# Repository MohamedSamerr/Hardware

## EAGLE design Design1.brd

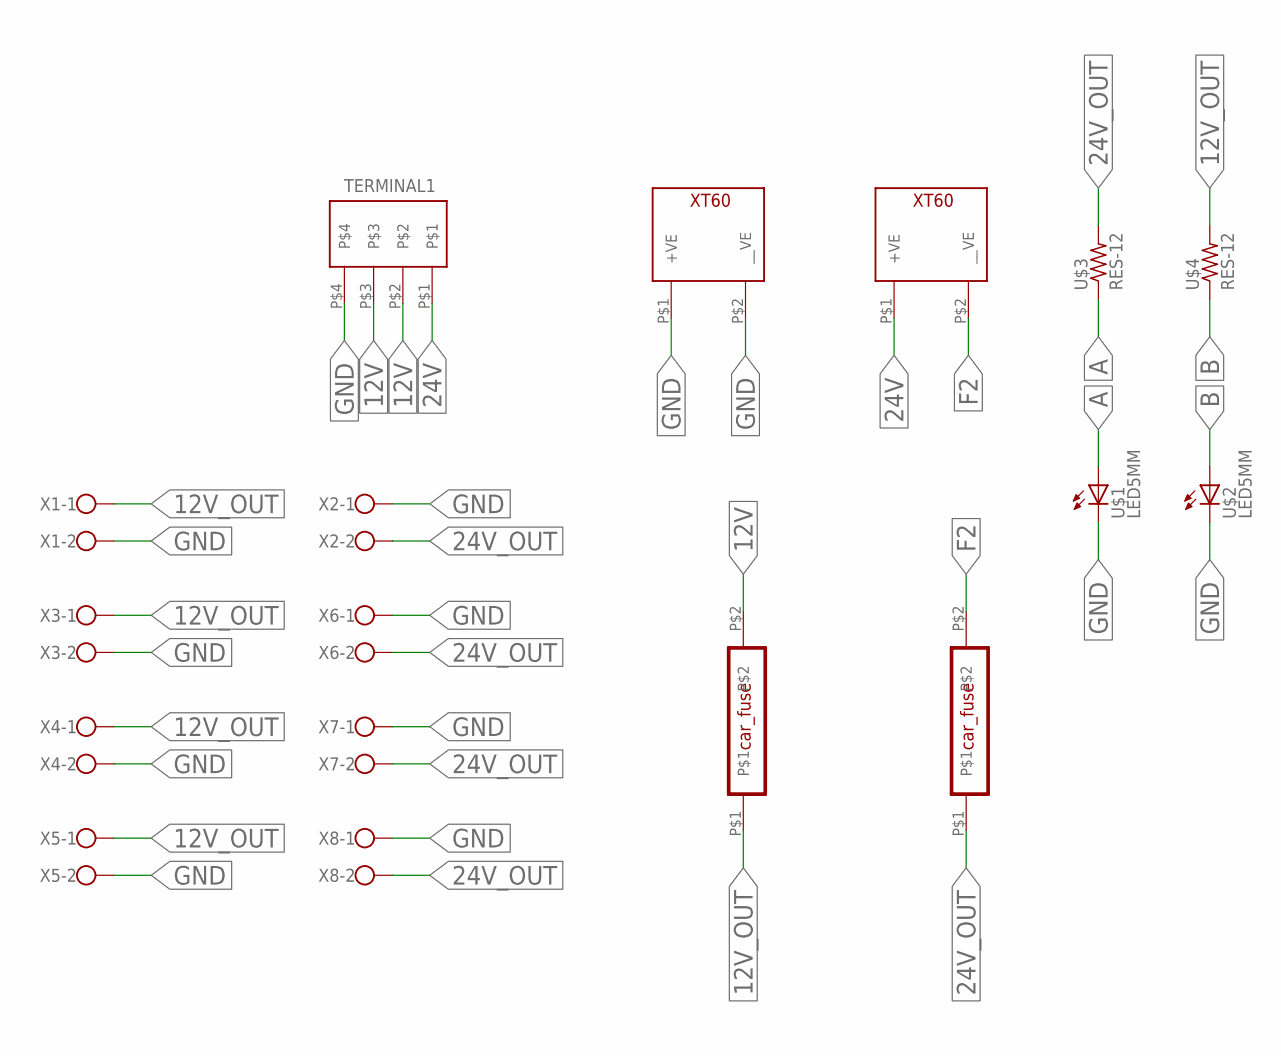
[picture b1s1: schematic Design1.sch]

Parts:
FUSE_12, FUSE_24: CAR_FUSE
SWITCH_12, SWITCH_24: XT60_CONNECTOR; XT60
TERMINAL1: BARRIER_TERMINAL_BLOCK_4PIN_9.5MM
U$1, U$2: LED5MM
U$3, U$4: RES-12; 0207/12
X1, X2, X3, X4, X5, X6, X7, X8: ROSTA.POWER; W239-302

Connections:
12V: FUSE_12.P$2, TERMINAL1.P$2, TERMINAL1.P$3
12V_OUT: FUSE_12.P$1, U$4.2, X1.1, X3.1, X4.1, X5.1
24V: SWITCH_24.P$1 (+VE), TERMINAL1.P$1
24V_OUT: FUSE_24.P$1, U$3.2, X2.2, X6.2, X7.2, X8.2
A: U$1.A, U$3.1
B: U$2.A, U$4.1
F2: FUSE_24.P$2, SWITCH_24.P$2 (__VE)
GND: SWITCH_12.P$1 (+VE), SWITCH_12.P$2 (__VE), TERMINAL1.P$4, U$1.K (C), U$2.K (C), X1.2, X2.1, X3.2, X4.2, X5.2, X6.1, X7.1, X8.1

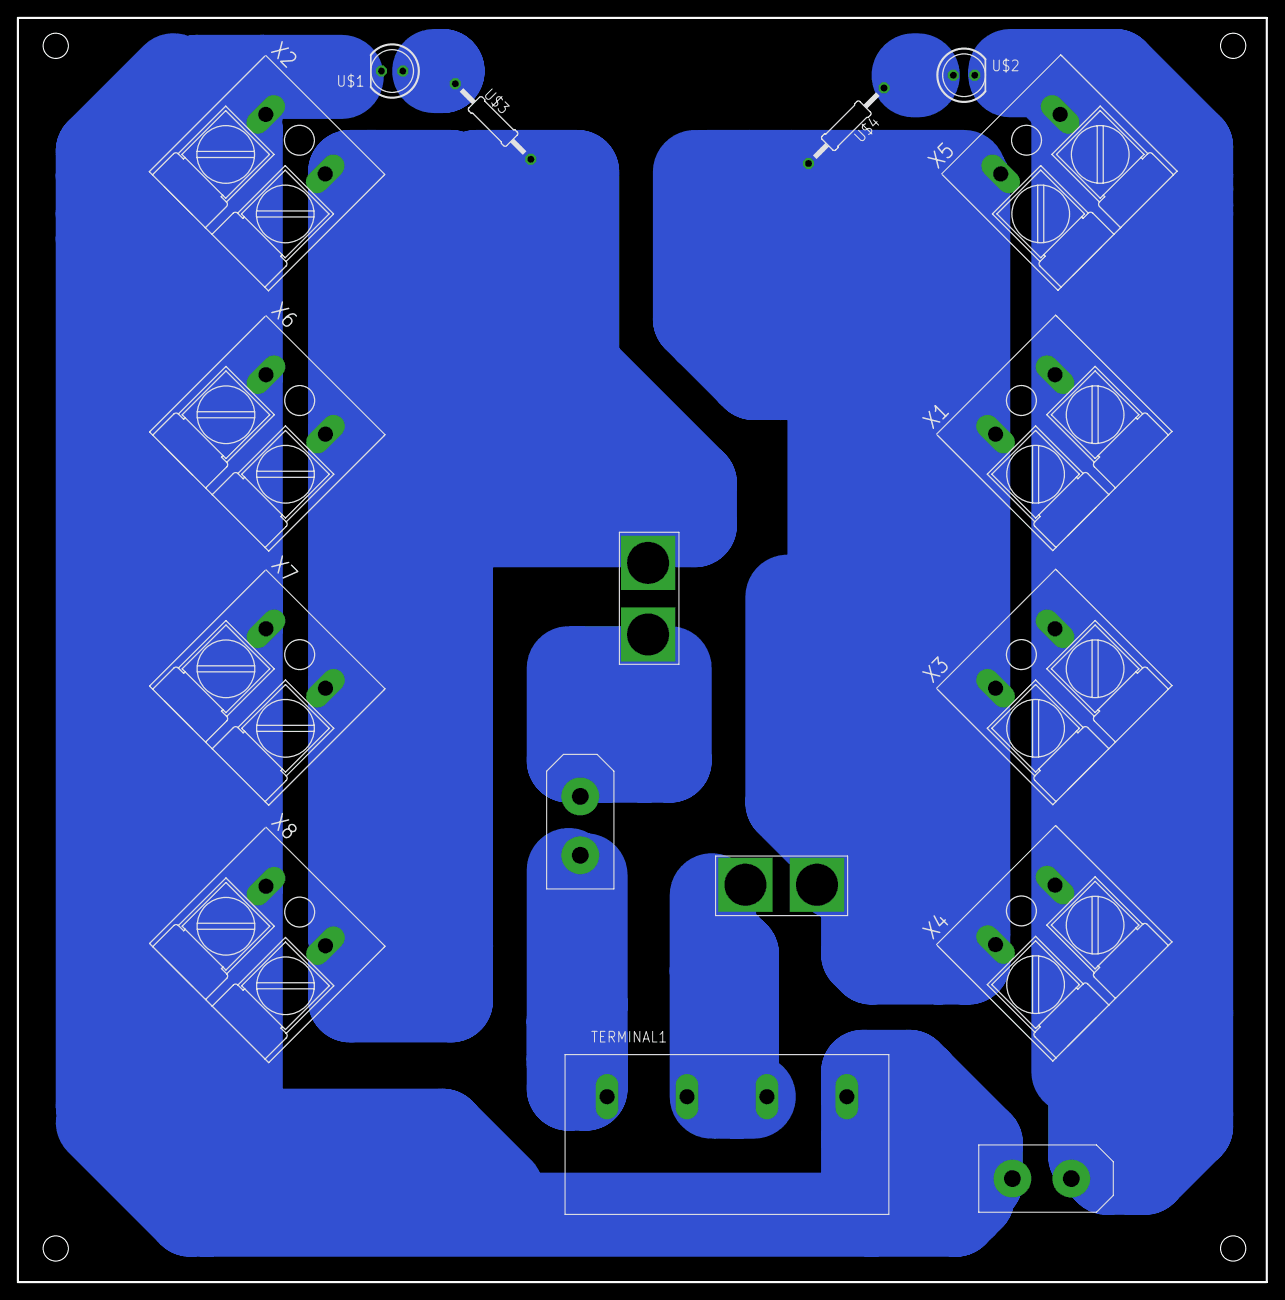
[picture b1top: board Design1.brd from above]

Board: 2 copper layers, 148.5 x 150.3 mm, 17 parts (0 on the bottom side), 8 nets.

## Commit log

2022-12-13 added design
2022-12-16 added tracks
